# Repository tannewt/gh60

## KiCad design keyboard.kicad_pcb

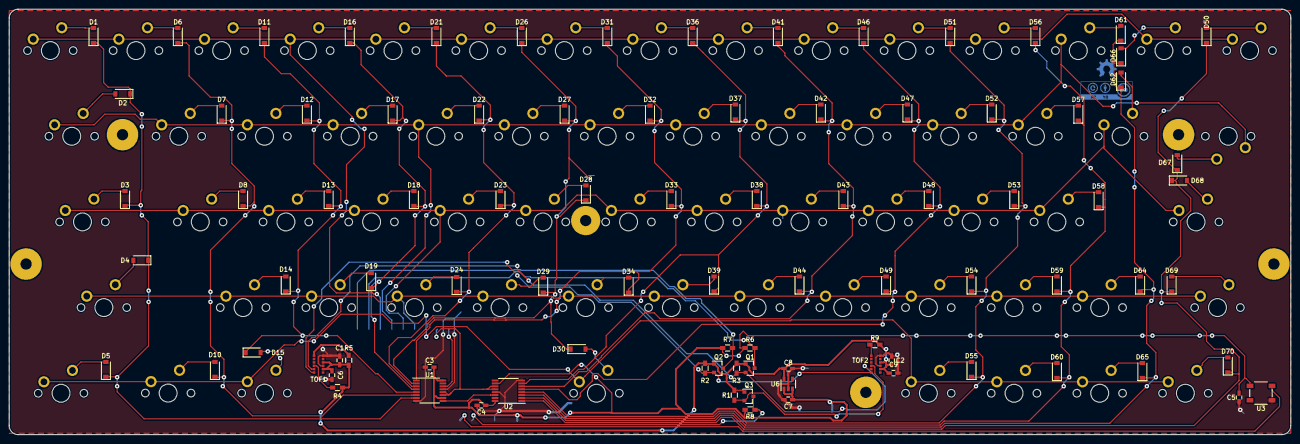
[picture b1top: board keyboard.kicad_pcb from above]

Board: 2 copper layers, 285.0 x 94.6 mm, 160 parts (1 on the bottom side), 98 nets.

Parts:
C1, C2: .1uF; C_0603_HandSoldering
C3, C4, C5: 0.1uF; C_0603_HandSoldering
C6, C9: 4.7uF; C_0603_HandSoldering
C7, C8: 10uF; C_0603_HandSoldering
D1, D2, D3, D4, D5, D6, D7, D8, D10, D11, D12, D13, D14, D15, D16, D17, D18, D19, D21, D22, D23, D24, D26, D27, D28, D29, D30, D31, D32, D33, D34, D36, D37, D38, D39, D41, D42, D43, D44, D46, D47, D48, D49, D50, D51, D52, D53, D54, D55, D56, D57, D58, D59, D60, D61, D62, D64, D65, D66, D67, D68, D69, D70: 1N4148; D_SOD-123
HOLE: VAL**; PKRHC
HOLE#2, HOLE#3, HOLE#4, HOLE#5, HOLE#6: VAL**; PKRHC
Q1, Q2, Q3: BSS138; SOT-23
R1, R2, R3, R6, R7, R8: 10K; R_0603_HandSoldering
R4, R5, R9: 47K; R_0603_HandSoldering
S1, S6, S7, S8, S11, S12, S13, S14, S16, S17, S18, S19, S21, S22, S23, S24, S26, S27, S28, S29, S31, S32, S33, S34, S36, S37, S38, S39, S41, S42, S43, S44, S46, S47, S48, S49, S50, S51, S52, S53, S54, S56, S57, S58, S59, S61, S62, S64, S70, S552, S601, S661, S6512: MX1A; MX1A-1U
S_caps1: MX1A; MX1A-1.75U
S_enter1: MX1A; MX1A-2.25U
S_lshift1: MX1A; MX1A-2.25U
S_mod1, S_mod2: MX1A; MX1A-1.25U
S_rshift1: MX1A; MX1A-1.75U
S_slash1: MX1A; MX1A-1.5U
S_tab1: MX1A; MX1A-1.5U
Smod3: MX1A; MX1A-1U
TOF1, TOF2: VL6180X
U1, U2: 74HC595; TSSOP-16_4.4x5mm_Pitch0.65mm
U3: SK6812
U5: FEATHER; Feather-SMD
U6: MIC5225_2.8V; SOT-23-5
spacebar1: MX1A; MX1A-6.25U

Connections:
/COL1: D1.1, D2.1, D3.1, D4.1, D5.1, U1.7
/COL2: D6.1, D7.1, D8.1, D10.1, U1.6
/COL3: D11.1, D12.1, D13.1, D14.1, D15.1, U1.5
/COL4: D16.1, D17.1, D18.1, D19.1, U1.4
/COL5: D21.1, D22.1, D23.1, D24.1, U1.3
/COL6: D26.1, D27.1, D28.1, D29.1, D30.1, U1.2
/COL7: D31.1, D32.1, D33.1, D34.1, U1.1
/COL8: D36.1, D37.1, D38.1, D39.1, U2.7
/COL9: D41.1, D42.1, D43.1, D44.1, U2.6
/COL10: D46.1, D47.1, D48.1, D49.1, U2.5
/COL11: D51.1, D52.1, D53.1, D54.1, D55.1, U2.4
/COL12: D56.1, D57.1, D58.1, D59.1, D60.1, U2.3
/COL13: D61.1, D62.1, D64.1, D65.1, D66.1, U2.2
/COL14: D50.1, D67.1, D68.1, D69.1, D70.1, U2.1
/COL_CLK: U1.11, U1.12, U2.11, U2.12, U5.24
/COL_DATA: U1.14, U5.25
/NEOPIX: U3.2, U5.7
/ROW1: S1.1, S6.1, S11.1, S16.1, S21.1, S26.1, S31.1, S36.1, S41.1, S46.1, S50.1, S51.1, S56.1, S661.1, U5.19
/ROW2: S7.1, S12.1, S17.1, S22.1, S27.1, S32.1, S37.1, S42.1, S47.1, S52.1, S57.1, S61.1, S_slash1.1, S_tab1.1, U5.20
/ROW3: S8.1, S13.1, S18.1, S23.1, S28.1, S33.1, S38.1, S43.1, S48.1, S53.1, S58.1, S62.1, S_caps1.1, S_enter1.1, U5.21
/ROW4: S14.1, S19.1, S24.1, S29.1, S34.1, S39.1, S44.1, S49.1, S54.1, S59.1, S64.1, S_lshift1.1, S_rshift1.1, U5.22
/ROW5: S70.1, S552.1, S601.1, S6512.1, S_mod1.1, S_mod2.1, Smod3.1, U5.23, spacebar1.1
/TOF2_CE: Q3.3, R8.2, U5.6
/TOF2_CE_28: Q3.2, R1.2, TOF2.4
/TOF_SCL: Q1.3, R6.2, U5.18
/TOF_SCL_28: Q1.2, R3.2, TOF1.5, TOF2.5
/TOF_SDA: Q2.3, R7.2, U5.17
/TOF_SDA_28: Q2.2, R2.2, TOF1.6, TOF2.6
GND: C1.1, C2.1, C3.2, C4.2, C5.2, C6.2, C7.1, C8.1, C9.2, TOF1.9, TOF1.12, TOF2.9, TOF2.12, U1.8, U1.13, U2.8, U2.13, U3.1, U5.4, U6.2
unnamed: D1.2, S1.2
unnamed: D2.2, S_tab1.2
unnamed: D3.2, S_caps1.2
unnamed: D4.2, S_lshift1.2
unnamed: D5.2, S_mod1.2
unnamed: D6.2, S6.2
unnamed: D7.2, S7.2
unnamed: D8.2, S8.2
unnamed: D10.2, S_mod2.2
unnamed: D11.2, S11.2
unnamed: D12.2, S12.2
unnamed: D13.2, S13.2
unnamed: D14.2, S14.2
unnamed: D15.2, Smod3.2
unnamed: D16.2, S16.2
unnamed: D17.2, S17.2
unnamed: D18.2, S18.2
unnamed: D19.2, S19.2
unnamed: D21.2, S21.2
unnamed: D22.2, S22.2
unnamed: D23.2, S23.2
unnamed: D24.2, S24.2
unnamed: D26.2, S26.2
unnamed: D27.2, S27.2
unnamed: D28.2, S28.2
unnamed: D29.2, S29.2
unnamed: D30.2, spacebar1.2
unnamed: D31.2, S31.2
unnamed: D32.2, S32.2
unnamed: D33.2, S33.2
unnamed: D34.2, S34.2
unnamed: D36.2, S36.2
unnamed: D37.2, S37.2
unnamed: D38.2, S38.2
unnamed: D39.2, S39.2
unnamed: D41.2, S41.2
unnamed: D42.2, S42.2
unnamed: D43.2, S43.2
unnamed: D44.2, S44.2
unnamed: D46.2, S46.2
unnamed: D47.2, S47.2
unnamed: D48.2, S48.2
unnamed: D49.2, S49.2
unnamed: D50.2, S50.2
unnamed: D51.2, S51.2
unnamed: D52.2, S52.2
unnamed: D53.2, S53.2
unnamed: D54.2, S54.2
unnamed: D55.2, S552.2
unnamed: D56.2, S56.2
unnamed: D57.2, S57.2
unnamed: D58.2, S58.2
unnamed: D59.2, S59.2
unnamed: D60.2, S601.2
unnamed: D61.2, S61.2
unnamed: D62.2, S62.2
unnamed: D64.2, S64.2
unnamed: D65.2, S6512.2
unnamed: D66.2, S661.2
unnamed: D67.2, S_slash1.2
unnamed: D68.2, S_enter1.2
unnamed: D69.2, S_rshift1.2
unnamed: D70.2, S70.2
unnamed: R4.2, TOF1.4
unnamed: R5.2, TOF1.1
unnamed: R9.2, TOF2.1
unnamed: U1.9, U2.14
VCC: C3.1, C4.1, C5.1, C7.2, R6.1, R7.1, R8.1, U1.10, U1.16, U2.10, U2.16, U3.3, U5.2, U6.1, U6.3
VDD: C1.2, C2.2, C6.1, C8.2, C9.1, Q1.1, Q2.1, Q3.1, R1.1, R2.1, R3.1, R4.1, R5.1, R9.1, TOF1.8, TOF1.10, TOF2.8, TOF2.10, U6.5

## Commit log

2017-01-19 Incomplete layout with IO expanders only. Next will switch back to matrix.
2017-01-19 Switch to a matrix. Not done yet because feather needs to move.
2017-02-01 Working version with closer to correct NeoPixel footprint.
